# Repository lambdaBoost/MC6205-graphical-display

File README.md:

# MC6205-graphical-display
graphical display on old neon plasma screen. 

<p align="center">
  
  <figcaption><i>I'm showing this because it's funny - tracking wrecked Soviet era vehicles on a Soviet era device. Also, note the dead display line on the 'abandoned' section. We'll fix that later.</i></figcaption>
</p>

This is a two part project using the Soviet Ukrainian MC6205 plasma display.
Part 1 uses the unaltered device with an ESP32 in order to display text info from any suitable webpage or API.
Part 2 will convert the device into a full graphical display (ie not just text).

## MC6205 Intro
The device itself is a monochrome neon plasma display, produced throughout the 1980s and early 1990s in Soviet Ukraine. It is capable of displaying text on a 100x100px screen. This is achieved by supplying appropriate serial inputs to the 64 pin connector on the base of the display.
Included in the package is an EEPROM which converts the serial inputs into text characters. This unfortunately mean the MC6205 is only capable of displaying text, but part 2 will see me re-wiring and adding a custom PCB to allow for full graphical display.

## Vehicle Loss Tracker
To demo part 1, I'm using the device to provide live updates on Russian vehicle losses. Data is from the excellent [Oryx loss tracker](https://www.oryxspioenkop.com/2022/02/attack-on-europe-documenting-equipment.html)

Fortunately someone else did the hard work and wrote an arduino library [arduino library](https://github.com/holzachr/MS6205-arduino-library) to display text to the display, so all I needed to do was hook it up to the ESP32 (following the instructions from the linked repo).

Data is provided by a custom API which runs on a seperate machine. In my case, the API runs from a raspberry pi and is queried by the ESP32. This avoided having to attempt to parse the webpage in Arduino...which would be a nightmare. The code for part 2 will be in Micropython which I find much easier to work with.

For now, the setup is wired up via a breadboard. When part 2 is complete it will be entirely contained in the original enclosure.

<p align="center">
  
  <figcaption><i>It's a clock too, because why not.</i></figcaption>
</p>

## Prerequisites
To build the vehicle tracker display in the exact format shown here you will need:

* MC6205 display. Available on ebay...but they are gradually getting more and more expensive!
* Raspberry pi with docker installed
* SN74HC595 shift register
* ESP32 WROOM development board
* A lot of hookup wire
* [MS6205-arduino-library](https://github.com/holzachr/MS6205-arduino-library) installed in your Arduino libraries folder
* 12v power supply (mine is 1A)

## Instructions
To build the vehicle loss tracker do the following:

* Hook up the MC6205 to the ESP32 and 12v power supply as detailed in [holzachr's repo](https://github.com/holzachr/MS6205-arduino-library)
* clone this repo to the raspberry pi
* on the pi, cd into the web-scraper directory
* then build and run the docker container with: `docker-compose up -d`
* the API should now be active - note the pi's IP address (`ifconfig`)
* open the file at /mc6205/vehicle_loss_tracker.ino
* edit the first 3 lines (after the library imports) to include the correct IP address for the pi, your wifi network SSID and your wifi password (this is a lazy way of getting credentials - I'll add a proper wifi manager later).
* upload the edited .ino file to the esp32. I had to disconnect GPIO12 during the upload for it to work.
* Enjoy!

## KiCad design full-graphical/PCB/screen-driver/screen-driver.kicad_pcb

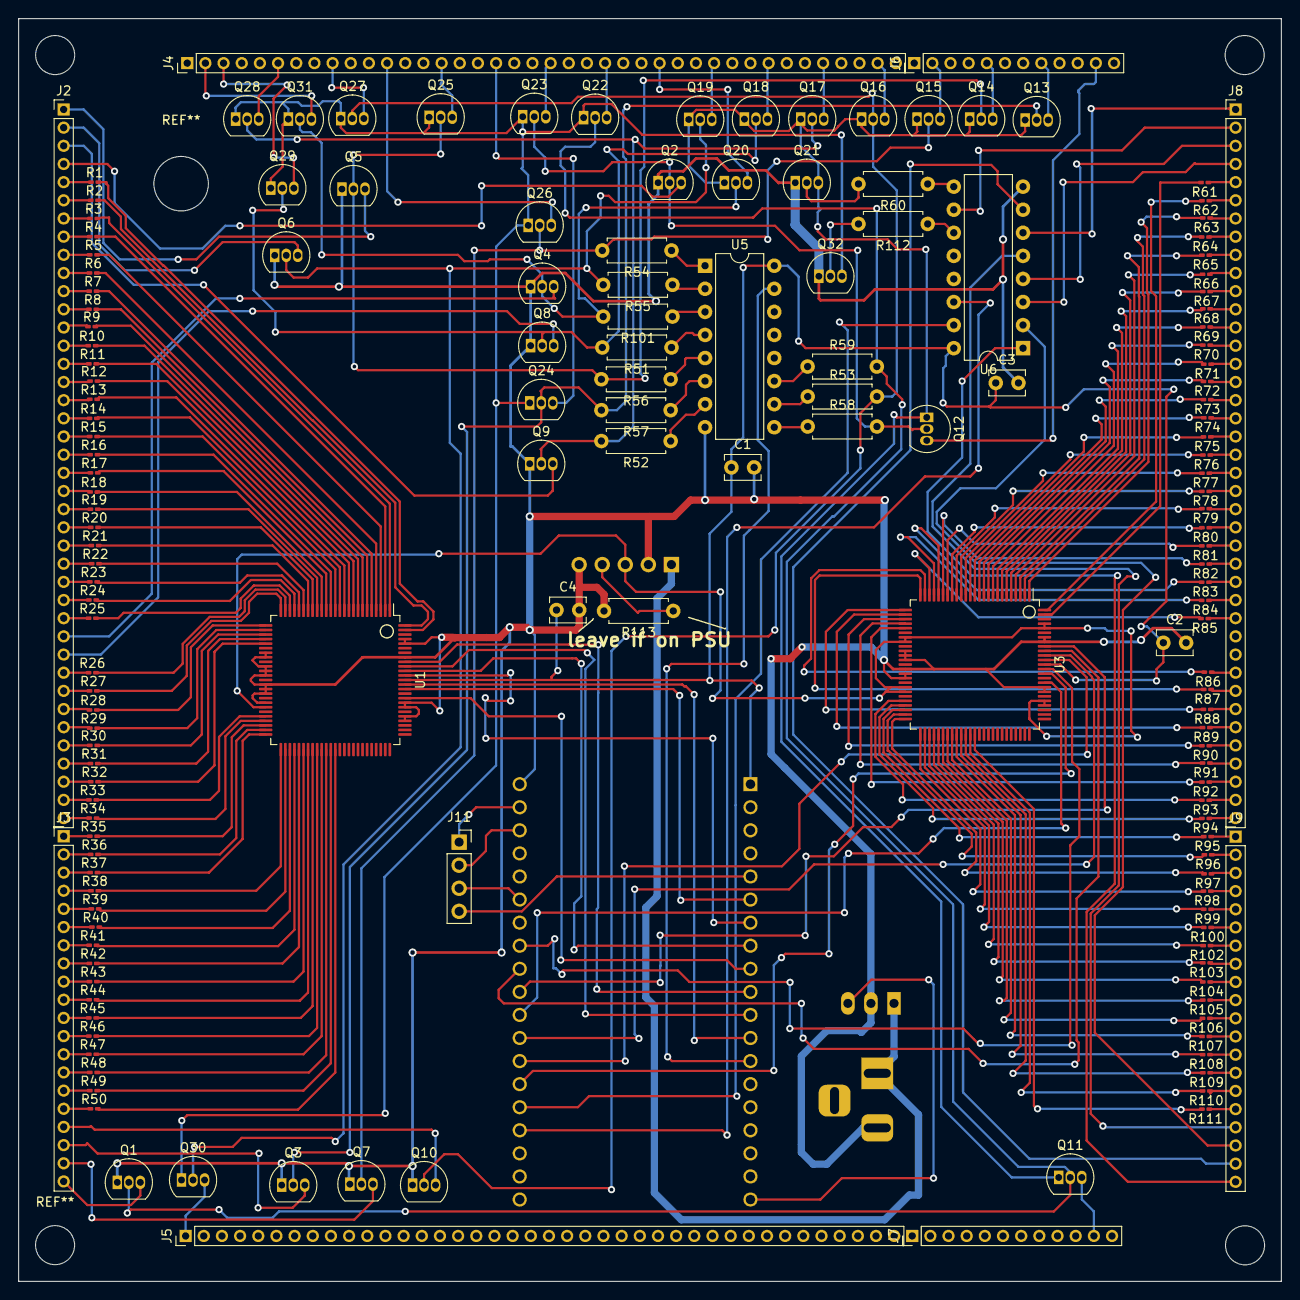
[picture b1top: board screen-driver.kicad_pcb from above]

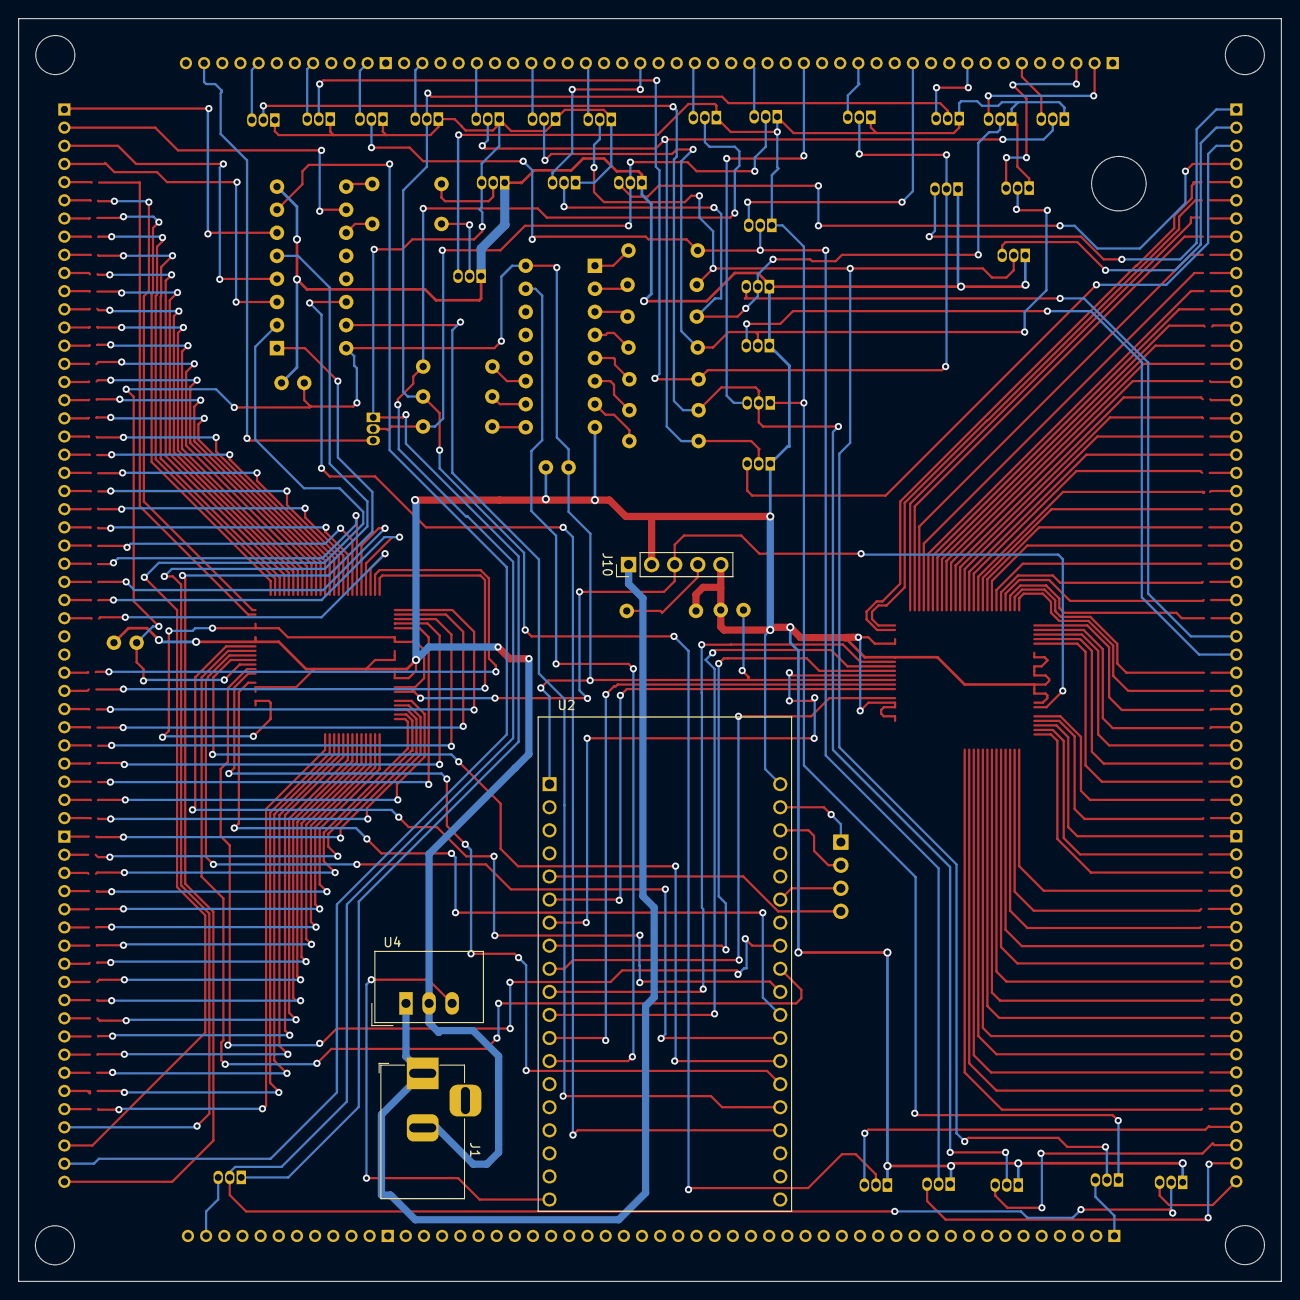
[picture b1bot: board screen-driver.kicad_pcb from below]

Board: 2 copper layers, 139.0 x 139.0 mm, 166 parts (4 on the bottom side), 291 nets.

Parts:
C1, C2, C3, C4: C_Small; C_Disc_D3.8mm_W2.6mm_P2.50mm
J1: Barrel_Jack_Switch; BarrelJack_Horizontal
J2: ANODE - EVEN 2-60; PinHeader_1x40_P2.00mm_Vertical
J3: ANODE - EVEN-62-100; PinHeader_1x20_P2.00mm_Vertical
J4: CATHODE - EVEN - 42-100; PinHeader_1x40_P2.00mm_Vertical
J5: CATHODE ODD 41-99; PinHeader_1x40_P2.00mm_Vertical
J6: CATHODE EVEN 2-40; PinHeader_1x12_P2.00mm_Vertical
J7: CATHODE ODD 1-39; PinHeader_1x12_P2.00mm_Vertical
J8: ANODE - ODD 1-59; PinHeader_1x40_P2.00mm_Vertical
J9: ANODE - ODD 61-99; PinHeader_1x20_P2.00mm_Vertical
J10: Conn_01x05_Male; PinHeader_1x05_P2.54mm_Vertical
J11: Conn_01x04; PinSocket_1x04_P2.54mm_Vertical
Q1, Q2, Q3, Q4, Q5, Q6, Q7, Q8, Q9, Q10, Q11, Q12, Q13, Q14, Q15, Q16, Q17, Q18, Q19, Q20, Q21, Q22, Q23, Q24, Q25, Q26, Q27, Q28, Q29, Q30, Q31, Q32: MPSA42; TO-92_Inline
R1, R2, R3, R4, R5, R6, R7, R8, R9, R10, R11, R12, R13, R14, R15, R16, R17, R18, R19, R20, R21, R22, R23, R24, R25, R26, R27, R28, R29, R30, R31, R32, R33, R34, R35, R36, R37, R38, R39, R40, R41, R42, R43, R44, R45, R46, R47, R48, R49, R50, R61, R62, R63, R64, R65, R66, R67, R68, R69, R70, R71, R72, R73, R74, R75, R76, R77, R78, R79, R80, R81, R82, R83, R84, R85, R86, R87, R88, R89, R90, R91, R92, R93, R94, R95, R96, R97, R98, R99, R100, R102, R103, R104, R105, R106, R107, R108, R109, R110, R111: R; R_0201_0603Metric_Pad0.64x0.40mm_HandSolder
R51, R52, R53, R54, R55, R56, R57, R58, R59, R60, R101, R112, R113: R; R_Axial_DIN0207_L6.3mm_D2.5mm_P7.62mm_Horizontal
U1, U3: SN755870; TQFP-100_14x14mm_P0.5mm
U2: ESP32-DEVKITC-32D; MODULE_ESP32-DEVKITC-32D
U4: TSR_1-2450; Converter_DCDC_TRACO_TSR-1_THT
U5, U6: CD4017BE; DIP-16_W7.62mm

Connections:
+3V3: C1.1, C2.1, C3.1, C4.1, U1.88 (VDD), U2.1 (3V3), U3.88 (VDD), U5.16 (VDD), U6.16 (VDD)
+5V: U2.19 (EXT_5V), U4.3 (Vout)
GND: C1.2, C2.2, C3.2, C4.2, J1.2, J10.2, J10.5, Q1.1 (E), Q2.1 (E), Q3.1 (E), Q4.1 (E), Q5.1 (E), Q6.1 (E), Q7.1 (E), Q8.1 (E), Q9.1 (E), Q10.1 (E), Q21.1 (E), Q32.1 (E), R113.2, U1.32 (VDDH), U1.33 (VDDH), U1.35 (GND1), U1.36 (GND1), U1.37 (GND1), U1.39 (GND2), U1.40 (GND1), U1.41 (GND1), U1.43 (VDDH), U1.79 (VDDH), U1.80 (VDDH), U1.82 (GND1), U1.83 (GND1), U1.93 (GND1), U1.96 (VDDH), U1.97 (VDDH), U2.20 (GND3), U3.35 (GND1), U3.36 (GND1), U3.37 (GND1), U3.39 (GND2), U3.40 (GND1), U3.41 (GND1), U3.82 (GND1), U3.83 (GND1), U3.93 (GND1), U3.94 (GND1), U4.2 (GND), U5.8 (VSS), U6.8 (VSS)
unnamed: J1.1, J10.1, U4.1 (Vin)
unnamed: J2.1, Q5.3 (C)
unnamed: J2.2, Q6.3 (C)
unnamed: J2.3, Q9.3 (C)
unnamed: J2.4, Q2.3 (C)
unnamed: J2.5, R1.1
unnamed: J2.6, R2.1
unnamed: J2.7, R3.1
unnamed: J2.8, R4.1
unnamed: J2.9, R5.1
unnamed: J2.10, R6.1
unnamed: J2.11, R7.1
unnamed: J2.12, R8.1
unnamed: J2.13, R9.1
unnamed: J2.14, R10.1
unnamed: J2.15, R11.1
unnamed: J2.16, R12.1
unnamed: J2.17, R13.1
unnamed: J2.18, R14.1
unnamed: J2.19, R15.1
unnamed: J2.20, R16.1
unnamed: J2.21, R17.1
unnamed: J2.22, R18.1
unnamed: J2.23, R19.1
unnamed: J2.24, R20.1
unnamed: J2.25, R21.1
unnamed: J2.26, R22.1
unnamed: J2.27, R23.1
unnamed: J2.28, R24.1
unnamed: J2.29, R25.1
unnamed: J2.30, Q4.3 (C)
unnamed: J2.31, Q8.3 (C)
unnamed: J2.32, R26.1
unnamed: J2.33, R27.1
unnamed: J2.34, R28.1
unnamed: J2.35, R29.1
unnamed: J2.36, R30.1
unnamed: J2.37, R31.1
unnamed: J2.38, R32.1
unnamed: J2.39, R33.1
unnamed: J2.40, R34.1
unnamed: J3.1, R35.1
unnamed: J3.2, R36.1
unnamed: J3.3, R37.1
unnamed: J3.4, R38.1
unnamed: J3.5, R39.1
unnamed: J3.6, R40.1
unnamed: J3.7, R41.1
unnamed: J3.8, R42.1
unnamed: J3.9, R43.1
unnamed: J3.10, R44.1
unnamed: J3.11, R45.1
unnamed: J3.12, R46.1
unnamed: J3.13, R47.1
unnamed: J3.14, R48.1
unnamed: J3.15, R49.1
unnamed: J3.16, R50.1
unnamed: J3.17, Q10.3 (C)
unnamed: J3.18, Q3.3 (C)
unnamed: J3.19, Q7.3 (C)
unnamed: J3.20, Q1.3 (C)
unnamed: J4.2, Q31.3 (C)
unnamed: J4.3, Q29.3 (C)
unnamed: J4.6, Q28.3 (C)
unnamed: J4.9, Q27.3 (C)
unnamed: J4.12, Q26.3 (C)
unnamed: J4.15, Q25.3 (C)
unnamed: J4.18, Q24.3 (C)
unnamed: J4.21, Q23.3 (C)
unnamed: J4.24, Q22.3 (C)
unnamed: J4.27, Q20.3 (C)
unnamed: J4.30, Q19.3 (C)
unnamed: J4.33, Q18.3 (C)
unnamed: J4.36, Q17.3 (C)
unnamed: J4.39, Q16.3 (C)
unnamed: J5.1, Q30.3 (C)
unnamed: J6.2, Q15.3 (C)
unnamed: J6.5, Q14.3 (C)
unnamed: J6.8, Q13.3 (C)
unnamed: J6.11, Q12.3 (C)
unnamed: J7.11, Q11.3 (C)
unnamed: J8.1, U6.6 (7)
unnamed: J8.2, U6.10 (4)
unnamed: J8.3, U6.4 (2)
unnamed: J8.4, U6.3 (O)
unnamed: J8.5, R61.1
unnamed: J8.6, R62.1
unnamed: J8.7, R63.1
unnamed: J8.8, R64.1
unnamed: J8.9, R65.1
unnamed: J8.10, R66.1
unnamed: J8.11, R67.1
unnamed: J8.12, R68.1
unnamed: J8.13, R69.1
unnamed: J8.14, R70.1
unnamed: J8.15, R71.1
unnamed: J8.16, R72.1
unnamed: J8.17, R73.1
unnamed: J8.18, R74.1
unnamed: J8.19, R75.1
unnamed: J8.20, R76.1
unnamed: J8.21, R77.1
unnamed: J8.22, R78.1
unnamed: J8.23, R79.1
unnamed: J8.24, R80.1
unnamed: J8.25, R81.1
unnamed: J8.26, R82.1
unnamed: J8.27, R83.1
unnamed: J8.28, R84.1
unnamed: J8.29, R85.1
unnamed: J8.32, R86.1
unnamed: J8.33, R87.1
unnamed: J8.34, R88.1
unnamed: J8.35, R89.1
unnamed: J8.36, R90.1
unnamed: J8.37, R91.1
unnamed: J8.38, R92.1
unnamed: J8.39, R93.1
unnamed: J8.40, R94.1
unnamed: J9.1, R95.1
unnamed: J9.2, R96.1
unnamed: J9.3, R97.1
unnamed: J9.4, R98.1
unnamed: J9.5, R99.1
unnamed: J9.6, R100.1
unnamed: J9.7, R102.1
unnamed: J9.8, R103.1
unnamed: J9.9, R104.1
unnamed: J9.10, R105.1
unnamed: J9.11, R106.1
unnamed: J9.12, R107.1
unnamed: J9.13, R108.1
unnamed: J9.14, R109.1
unnamed: J9.15, R110.1
unnamed: J9.16, R111.1
unnamed: J9.17, U6.5 (6)
unnamed: J9.18, U6.2 (1)
unnamed: J9.19, U6.7 (3)
unnamed: J9.20, U6.1 (5)
unnamed: J10.3, U1.44 (VDDH), U3.32 (VDDH), U3.33 (VDDH), U3.43 (VDDH), U3.44 (VDDH), U3.79 (VDDH), U3.80 (VDDH), U3.96 (VDDH), U3.97 (VDDH)
unnamed: J10.4, R113.1
unnamed: Q1.2 (B), Q11.2 (B), Q22.2 (B), R59.2
unnamed: Q10.2 (B), Q16.2 (B), Q27.2 (B), R53.2
unnamed: Q11.1 (E), Q12.1 (E), Q13.1 (E), Q14.1 (E), Q15.1 (E), Q16.1 (E), Q17.1 (E), Q18.1 (E), Q19.1 (E), Q20.1 (E), Q21.3 (C)
unnamed: Q2.2 (B), Q12.2 (B), Q23.2 (B), R58.2
unnamed: Q3.2 (B), Q13.2 (B), Q24.2 (B), R57.2
unnamed: Q5.2 (B), Q14.2 (B), Q25.2 (B), R56.2
unnamed: Q7.2 (B), Q15.2 (B), Q26.2 (B), R54.2
unnamed: Q9.2 (B), Q17.2 (B), Q28.2 (B), R52.2
unnamed: Q8.2 (B), Q18.2 (B), Q29.2 (B), R51.2
unnamed: Q6.2 (B), Q19.2 (B), Q30.2 (B), R55.2
unnamed: Q4.2 (B), Q20.2 (B), Q31.2 (B), R101.2
unnamed: Q21.2 (B), R60.2
unnamed: Q22.1 (E), Q23.1 (E), Q24.1 (E), Q25.1 (E), Q26.1 (E), Q27.1 (E), Q28.1 (E), Q29.1 (E), Q30.1 (E), Q31.1 (E), Q32.3 (C)
unnamed: Q32.2 (B), R112.2
unnamed: R1.2, U1.99 (OUT1)
unnamed: R2.2, U1.100 (OUT2)
unnamed: R3.2, U1.1 (OUT3)
unnamed: R4.2, U1.2 (OUT4)
unnamed: R5.2, U1.3 (OUT5)
unnamed: R6.2, U1.4 (OUT6)
unnamed: R7.2, U1.5 (OUT7)
unnamed: R8.2, U1.6 (OUT8)
unnamed: R9.2, U1.7 (OUT9)
unnamed: R10.2, U1.8 (OUT10)
unnamed: R11.2, U1.9 (OUT11)
unnamed: R12.2, U1.10 (OUT12)
unnamed: R13.2, U1.11 (OUT13)
unnamed: R14.2, U1.12 (OUT14)
unnamed: R15.2, U1.13 (OUT15)
unnamed: R16.2, U1.14 (OUT16)
unnamed: R17.2, U1.15 (OUT17)
unnamed: R18.2, U1.16 (OUT18)
unnamed: R19.2, U1.17 (OUT19)
unnamed: R20.2, U1.18 (OUT20)
unnamed: R21.2, U1.19 (OUT21)
unnamed: R22.2, U1.20 (OUT22)
unnamed: R23.2, U1.21 (OUT23)
unnamed: R24.2, U1.22 (OUT24)
unnamed: R25.2, U1.23 (OUT25)
unnamed: R26.2, U1.24 (OUT26)
unnamed: R27.2, U1.25 (OUT27)
unnamed: R28.2, U1.26 (OUT28)
unnamed: R29.2, U1.27 (OUT29)
unnamed: R30.2, U1.28 (OUT30)
unnamed: R31.2, U1.29 (OUT31)
unnamed: R32.2, U1.30 (OUT32)
unnamed: R33.2, U1.46 (OUT33)
unnamed: R34.2, U1.47 (OUT34)
unnamed: R35.2, U1.48 (OUT35)
unnamed: R36.2, U1.49 (OUT36)
unnamed: R37.2, U1.50 (OUT37)
unnamed: R38.2, U1.51 (OUT38)
unnamed: R39.2, U1.52 (OUT39)
unnamed: R40.2, U1.53 (OUT40)
unnamed: R41.2, U1.54 (OUT41)
unnamed: R42.2, U1.55 (OUT42)
unnamed: R43.2, U1.56 (OUT43)
unnamed: R44.2, U1.57 (OUT44)
unnamed: R45.2, U1.58 (OUT45)
unnamed: R46.2, U1.59 (OUT46)
unnamed: R47.2, U1.60 (OUT47)
unnamed: R48.2, U1.61 (OUT48)
unnamed: R49.2, U1.62 (OUT49)
unnamed: R50.2, U1.63 (OUT50)
unnamed: R51.1, U5.4 (2)
unnamed: R52.1, U5.7 (3)
unnamed: R53.1, U5.10 (4)
unnamed: R54.1, U5.1 (5)
unnamed: R55.1, U5.2 (1)
unnamed: R56.1, U5.5 (6)
unnamed: R57.1, U5.6 (7)
unnamed: R58.1, U5.9 (8)
unnamed: R59.1, U5.11 (9)
unnamed: R60.1, U6.9 (8)
unnamed: R61.2, U3.99 (OUT1)
unnamed: R62.2, U3.100 (OUT2)
unnamed: R63.2, U3.1 (OUT3)
unnamed: R64.2, U3.2 (OUT4)
unnamed: R65.2, U3.3 (OUT5)
unnamed: R66.2, U3.4 (OUT6)
unnamed: R67.2, U3.5 (OUT7)
unnamed: R68.2, U3.6 (OUT8)
unnamed: R69.2, U3.7 (OUT9)
unnamed: R70.2, U3.8 (OUT10)
unnamed: R71.2, U3.9 (OUT11)
unnamed: R72.2, U3.10 (OUT12)
unnamed: R73.2, U3.11 (OUT13)
unnamed: R74.2, U3.12 (OUT14)
unnamed: R75.2, U3.13 (OUT15)
unnamed: R76.2, U3.14 (OUT16)
unnamed: R77.2, U3.15 (OUT17)
unnamed: R78.2, U3.16 (OUT18)
unnamed: R79.2, U3.17 (OUT19)
unnamed: R80.2, U3.18 (OUT20)
unnamed: R81.2, U3.19 (OUT21)
unnamed: R82.2, U3.20 (OUT22)
unnamed: R83.2, U3.21 (OUT23)
unnamed: R84.2, U3.22 (OUT24)
unnamed: R85.2, U3.23 (OUT25)
unnamed: R86.2, U3.24 (OUT26)
unnamed: R87.2, U3.25 (OUT27)
unnamed: R88.2, U3.26 (OUT28)
unnamed: R89.2, U3.27 (OUT29)
unnamed: R90.2, U3.28 (OUT30)
unnamed: R91.2, U3.29 (OUT31)
unnamed: R92.2, U3.30 (OUT32)
unnamed: R93.2, U3.46 (OUT33)
unnamed: R94.2, U3.47 (OUT34)
unnamed: R95.2, U3.48 (OUT35)
unnamed: R96.2, U3.49 (OUT36)
unnamed: R97.2, U3.50 (OUT37)
unnamed: R98.2, U3.51 (OUT38)
unnamed: R99.2, U3.52 (OUT39)
unnamed: R100.2, U3.53 (OUT40)
unnamed: R101.1, U5.3 (O)
unnamed: R102.2, U3.54 (OUT41)
unnamed: R103.2, U3.55 (OUT42)
unnamed: R104.2, U3.56 (OUT43)
unnamed: R105.2, U3.57 (OUT44)
unnamed: R106.2, U3.58 (OUT45)
unnamed: R107.2, U3.59 (OUT46)
unnamed: R108.2, U3.60 (OUT47)
unnamed: R109.2, U3.61 (OUT48)
unnamed: R110.2, U3.62 (OUT49)
unnamed: R111.2, U3.63 (OUT50)
unnamed: R112.1, U6.11 (9)
unnamed: U1.84 (DIR), U2.9 (IO25)
unnamed: U1.86 (CLK), U2.6 (IO35)
unnamed: U1.87 (LAT), U2.12 (IO14)
unnamed: U1.89 (OC1), U2.7 (IO32)
unnamed: U1.90 (OC2), U2.8 (IO33)
unnamed: U1.91 (SI), U2.11 (IO27)
unnamed: U1.92 (CLR), U2.10 (IO26)
unnamed: J11.4, U2.5 (IO34)
unnamed: J11.1, U2.21 (IO23)
unnamed: J11.2, U2.22 (IO22)
unnamed: J11.3, U2.25 (IO21)
unnamed: U2.27 (IO19), U3.87 (LAT)
unnamed: U2.28 (IO18), U3.91 (SI)
unnamed: U2.29 (IO5), U3.92 (CLR)
unnamed: U2.30 (IO17), U3.84 (DIR)
unnamed: U2.31 (IO16), U3.90 (OC2)
unnamed: U2.32 (IO4), U3.89 (OC1)
unnamed: U2.33 (IO0), U3.86 (CLK)
unnamed: U2.34 (IO2), U6.15 (RESET)
unnamed: U2.35 (IO15), U6.14 (CLOCK)
unnamed: U2.13 (IO12), U5.15 (RESET)

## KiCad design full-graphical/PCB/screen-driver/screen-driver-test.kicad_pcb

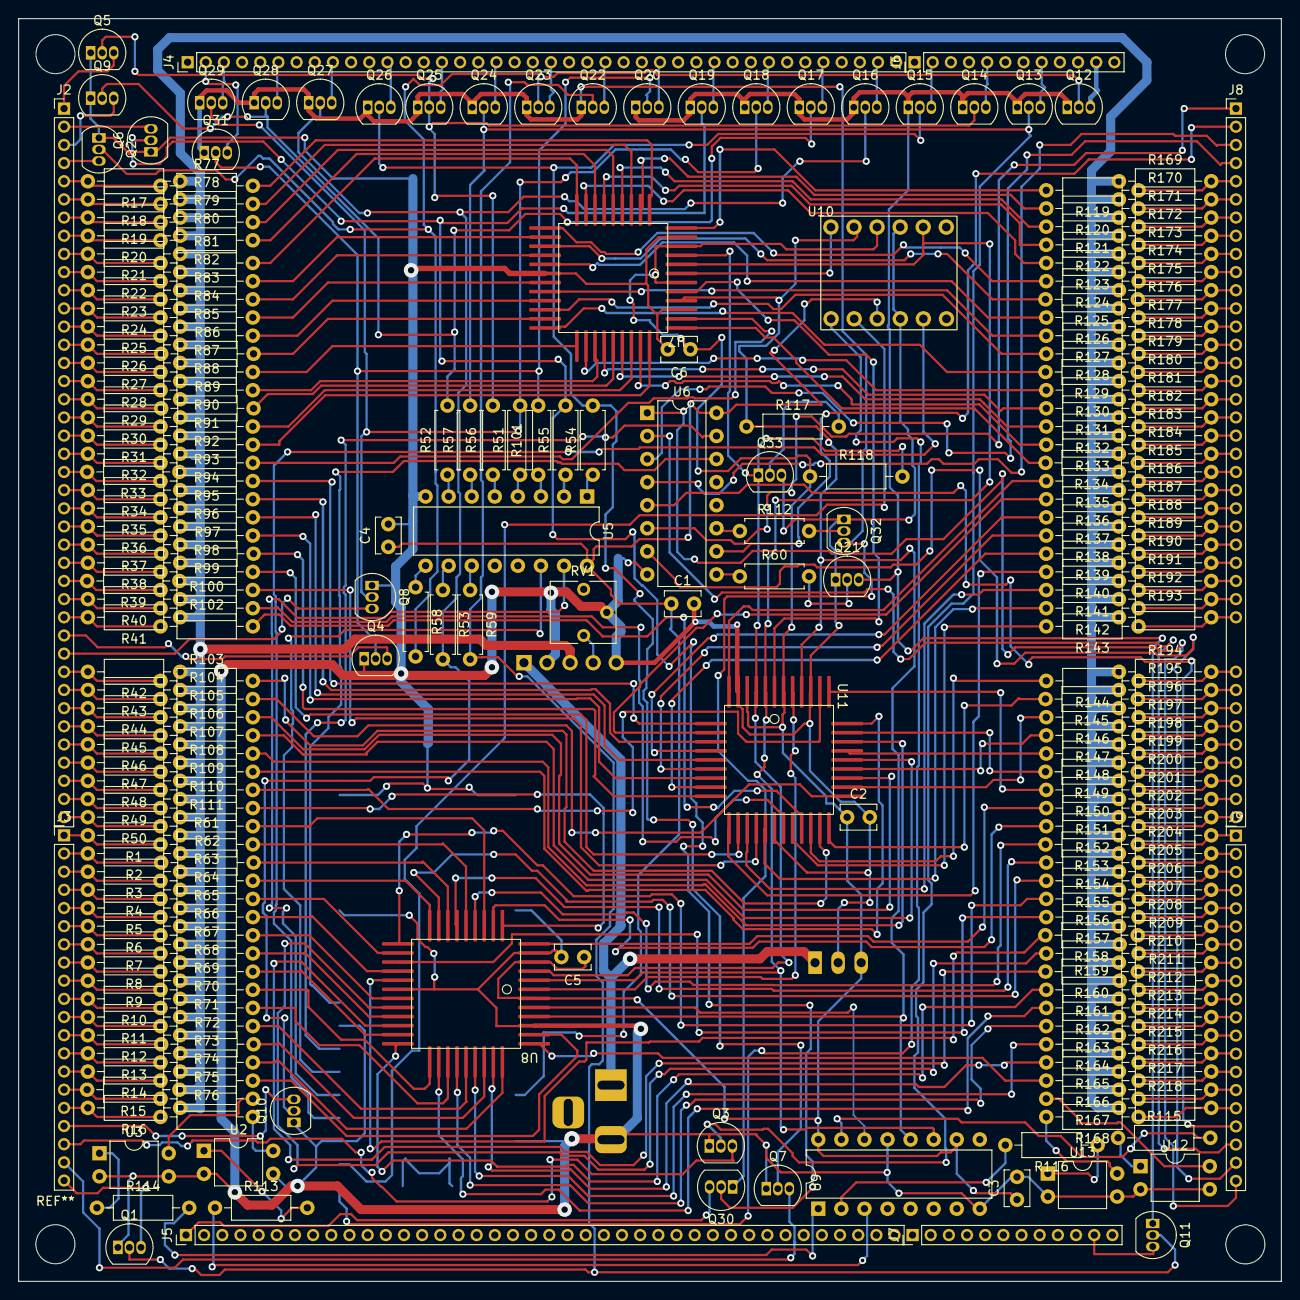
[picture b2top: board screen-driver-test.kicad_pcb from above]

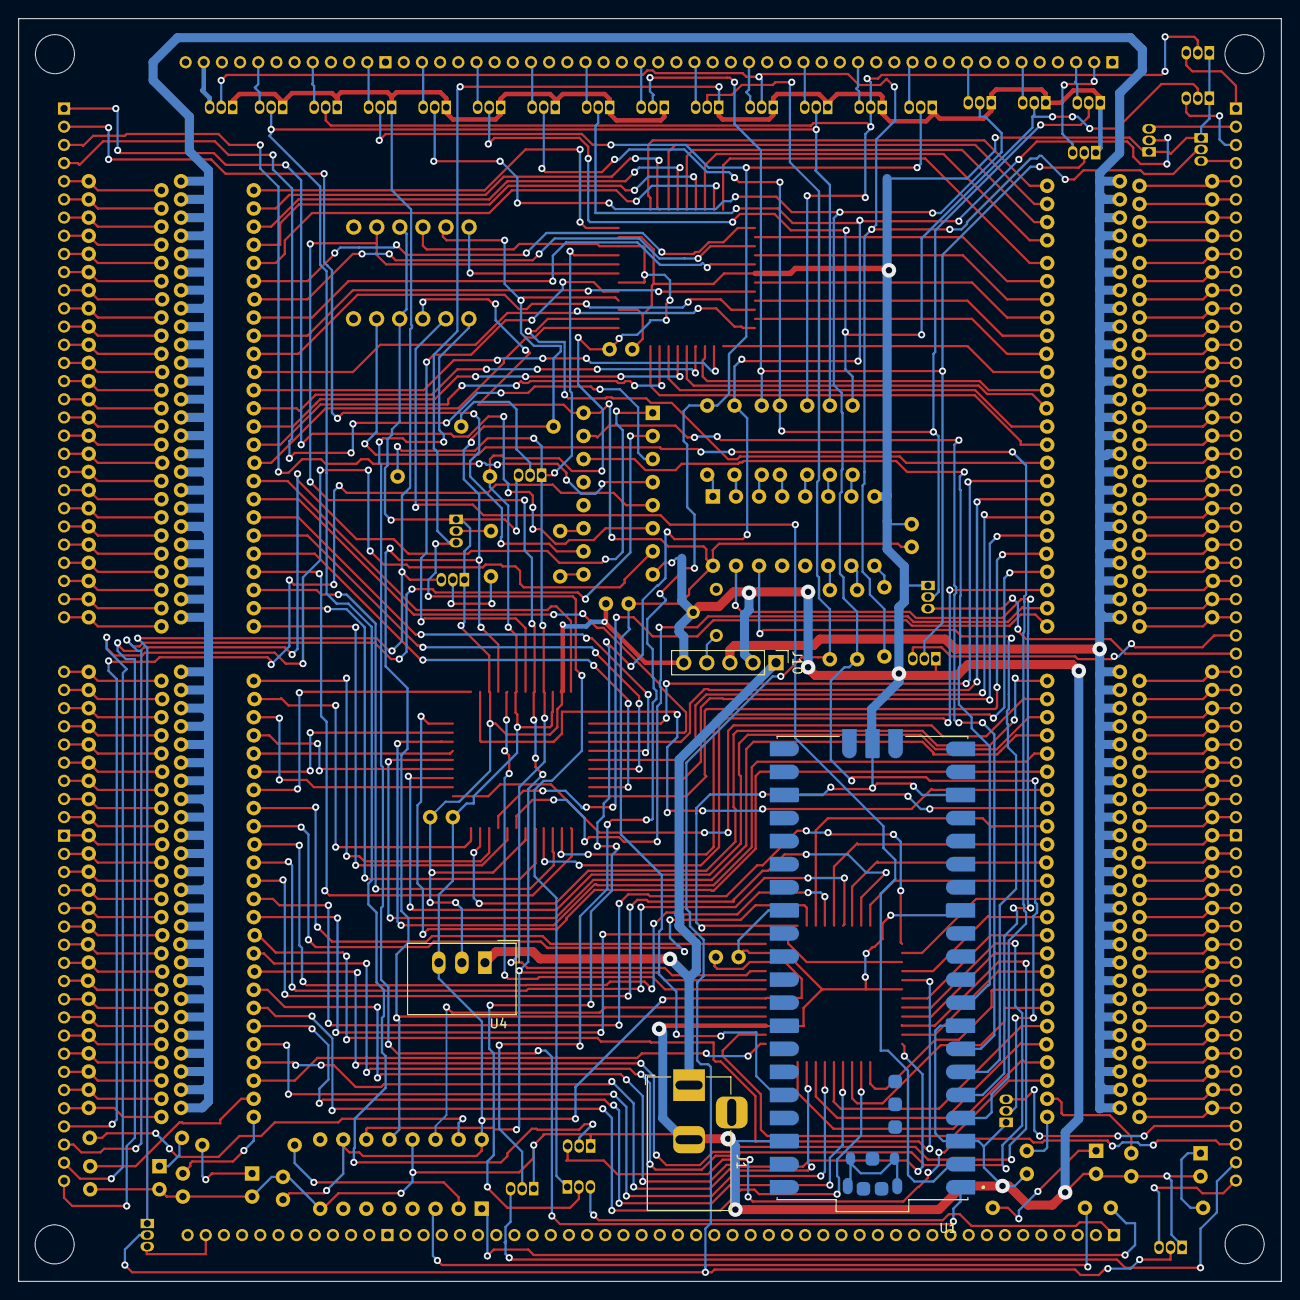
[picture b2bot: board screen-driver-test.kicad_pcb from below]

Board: 2 copper layers, 139.0 x 139.0 mm, 281 parts (4 on the bottom side), 294 nets.

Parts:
C1, C2, C3, C4, C5, C6: C_Small; C_Disc_D3.8mm_W2.6mm_P2.50mm
J1: Barrel_Jack_Switch; BarrelJack_Horizontal
J2: ANODE - EVEN 2-60; PinHeader_1x40_P2.00mm_Vertical
J3: ANODE - EVEN-62-100; PinHeader_1x20_P2.00mm_Vertical
J4: CATHODE - EVEN - 42-100; PinHeader_1x40_P2.00mm_Vertical
J5: CATHODE ODD 41-99; PinHeader_1x40_P2.00mm_Vertical
J6: CATHODE EVEN 2-40; PinHeader_1x12_P2.00mm_Vertical
J7: CATHODE ODD 1-39; PinHeader_1x12_P2.00mm_Vertical
J8: ANODE - ODD 1-59; PinHeader_1x40_P2.00mm_Vertical
J9: ANODE - ODD 61-99; PinHeader_1x20_P2.00mm_Vertical
J10: Conn_01x05_Male; PinHeader_1x05_P2.54mm_Vertical
Q1, Q2, Q3, Q4, Q5, Q6, Q7, Q8, Q9, Q10, Q11, Q12, Q13, Q14, Q15, Q16, Q17, Q18, Q19, Q20, Q21, Q22, Q23, Q24, Q25, Q26, Q27, Q28, Q29, Q30, Q31, Q32: MPSA42; TO-92_Inline
Q33: BC547; TO-92_Inline
R1, R2, R3, R4, R5, R6, R7, R8, R9, R10, R11, R12, R13, R14, R15, R16, R17, R18, R19, R20, R21, R22, R23, R24, R25, R26, R27, R28, R29, R30, R31, R32, R33, R34, R35, R36, R37, R38, R39, R40, R41, R42, R43, R44, R45, R46, R47, R48, R49, R50, R169, R170, R171, R172, R173, R174, R175, R176, R177, R178, R179, R180, R181, R182, R183, R184, R185, R186, R187, R188, R189, R190, R191, R192, R193, R194, R195, R196, R197, R198, R199, R200, R201, R202, R203, R204, R205, R206, R207, R208, R209, R210, R211, R212, R213, R214, R215, R216, R217, R218: 390k; R_Axial_DIN0207_L6.3mm_D2.5mm_P10.16mm_Horizontal
R51, R52, R53, R54, R55, R56, R57, R58, R59, R60, R101, R112: R; R_Axial_DIN0207_L6.3mm_D2.5mm_P7.62mm_Horizontal
R61, R62, R63, R64, R65, R66, R67, R68, R69, R70, R71, R72, R73, R74, R75, R76, R77, R78, R79, R80, R81, R82, R83, R84, R85, R86, R87, R88, R89, R90, R91, R92, R93, R94, R95, R96, R97, R98, R99, R100, R102, R103, R104, R105, R106, R107, R108, R109, R110, R111, R119, R120, R121, R122, R123, R124, R125, R126, R127, R128, R129, R130, R131, R132, R133, R134, R135, R136, R137, R138, R139, R140, R141, R142, R143, R144, R145, R146, R147, R148, R149, R150, R151, R152, R153, R154, R155, R156, R157, R158, R159, R160, R161, R162, R163, R164, R165, R166, R167, R168: 330k; R_Axial_DIN0207_L6.3mm_D2.5mm_P10.16mm_Horizontal
R113, R114, R115, R116: 330; R_Axial_DIN0207_L6.3mm_D2.5mm_P10.16mm_Horizontal
R117: 10k; R_Axial_DIN0207_L6.3mm_D2.5mm_P10.16mm_Horizontal
R118: 100; R_Axial_DIN0207_L6.3mm_D2.5mm_P10.16mm_Horizontal
RV1: R_Potentiometer; Potentiometer_Vishay_T73YP_Vertical
U1: SC0915; MODULE_SC0915
U2, U3, U12, U13: TLP627; DIP-4_W7.62mm
U4: TSR_1-2450; Converter_DCDC_TRACO_TSR-1_THT
U5, U6: CD4017BE; DIP-16_W7.62mm
U7, U8, U11: YH5504KH01
U9: 74HC595; DIP-16_W7.62mm
U10: level_converter; level_shifter

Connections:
+3V3: C1.1, C4.1, U1.36 (3V3_OUT), U5.16 (VDD), U6.16 (VDD), U10.3 (LV_in)
+5V: C2.1, C3.1, C5.1, C6.1, R118.1, U4.3 (Vout), U7.4 (VCC), U7.42 (VCC), U8.4 (VCC), U8.42 (VCC), U9.10 (~SRCLR), U9.16 (VCC), U10.10 (HV_in), U11.4 (VCC), U11.42 (VCC)
/clk: U7.2 (clk), U8.2 (clk), U9.11 (SRCLK), U10.8 (HV3), U11.2 (clk)
GND: C1.2, C2.2, C3.2, C4.2, C5.2, C6.2, J1.2, J10.2, J10.5, Q1.1 (E), Q2.1 (E), Q3.1 (E), Q4.1 (E), Q5.1 (E), Q6.1 (E), Q7.1 (E), Q8.1 (E), Q9.1 (E), Q10.1 (E), Q21.1 (E), Q32.1 (E), Q33.3 (E), RV1.2, U1.3 (GND), U1.8 (GND), U1.13 (GND), U1.18 (GND), U1.23 (GND), U1.28 (GND), U1.38 (GND), U1.D2 (GND), U2.2, U2.3, U3.2, U3.3, U4.2 (GND), U5.8 (VSS), U6.8 (VSS), U7.5 (gnd), U7.21 (gnd), U7.39 (gnd), U8.5 (gnd), U8.21 (gnd), U8.39 (gnd), U9.8 (GND), U9.13 (~OE), U10.4 (GND), U10.9 (GND), U11.5 (gnd), U11.21 (gnd), U11.39 (gnd), U12.2, U12.3, U13.2, U13.3
unnamed: J1.1, J10.1, U4.1 (Vin)
unnamed: J2.1, Q5.3 (C)
unnamed: J2.2, Q6.3 (C)
unnamed: J2.3, Q9.3 (C)
unnamed: J2.4, Q2.3 (C)
unnamed: J2.5, R17.2, R77.1
unnamed: J2.6, R18.2, R78.1
unnamed: J2.7, R19.2, R79.1
unnamed: J2.8, R20.2, R80.1
unnamed: J2.9, R21.2, R81.1
unnamed: J2.10, R22.2, R82.1
unnamed: J2.11, R23.2, R83.1
unnamed: J2.12, R24.2, R84.1
unnamed: J2.13, R25.2, R85.1
unnamed: J2.14, R26.2, R86.1
unnamed: J2.15, R27.2, R87.1
unnamed: J2.16, R28.2, R88.1
unnamed: J2.17, R29.2, R89.1
unnamed: J2.18, R30.2, R90.1
unnamed: J2.19, R31.2, R91.1
unnamed: J2.20, R32.2, R92.1
unnamed: J2.21, R33.2, R93.1
unnamed: J2.22, R34.2, R94.1
unnamed: J2.23, R35.2, R95.1
unnamed: J2.24, R36.2, R96.1
unnamed: J2.25, R37.2, R97.1
unnamed: J2.26, R38.2, R98.1
unnamed: J2.27, R39.2, R99.1
unnamed: J2.28, R40.2, R100.1
unnamed: J2.29, R41.2, R102.1
unnamed: J2.32, R42.2, R103.1
unnamed: J2.33, R43.2, R104.1
unnamed: J2.34, R44.2, R105.1
unnamed: J2.35, R45.2, R106.1
unnamed: J2.36, R46.2, R107.1
unnamed: J2.37, R47.2, R108.1
unnamed: J2.38, R48.2, R109.1
unnamed: J2.39, R49.2, R110.1
unnamed: J2.40, R50.2, R111.1
unnamed: J3.1, R1.2, R61.1
unnamed: J3.2, R2.2, R62.1
unnamed: J3.3, R3.2, R63.1
unnamed: J3.4, R4.2, R64.1
unnamed: J3.5, R5.2, R65.1
unnamed: J3.6, R6.2, R66.1
unnamed: J3.7, R7.2, R67.1
unnamed: J3.8, R8.2, R68.1
unnamed: J3.9, R9.2, R69.1
unnamed: J3.10, R10.2, R70.1
unnamed: J3.11, R11.2, R71.1
unnamed: J3.12, R12.2, R72.1
unnamed: J3.13, R13.2, R73.1
unnamed: J3.14, R14.2, R74.1
unnamed: J3.15, R15.2, R75.1
unnamed: J3.16, R16.2, R76.1
unnamed: J3.17, Q10.3 (C)
unnamed: J3.18, Q3.3 (C)
unnamed: J3.19, Q7.3 (C)
unnamed: J3.20, Q1.3 (C)
unnamed: J5.1, Q30.3 (C)
unnamed: J7.11, Q11.3 (C)
unnamed: J8.1, U6.6 (7)
unnamed: J8.2, U6.10 (4)
unnamed: J8.3, U6.4 (2)
unnamed: J8.4, U6.3 (O)
unnamed: J8.5, R119.1, R169.2
unnamed: J8.6, R120.1, R170.2
unnamed: J8.7, R121.1, R171.2
unnamed: J8.8, R122.1, R172.2
unnamed: J8.9, R123.1, R173.2
unnamed: J8.10, R124.1, R174.2
unnamed: J8.11, R125.1, R175.2
unnamed: J8.12, R126.1, R176.2
unnamed: J8.13, R127.1, R177.2
unnamed: J8.14, R128.1, R178.2
unnamed: J8.15, R129.1, R179.2
unnamed: J8.16, R130.1, R180.2
unnamed: J8.17, R131.1, R181.2
unnamed: J8.18, R132.1, R182.2
unnamed: J8.19, R133.1, R183.2
unnamed: J8.20, R134.1, R184.2
unnamed: J8.21, R135.1, R185.2
unnamed: J8.22, R136.1, R186.2
unnamed: J8.23, R137.1, R187.2
unnamed: J8.24, R138.1, R188.2
unnamed: J8.25, R139.1, R189.2
unnamed: J8.26, R140.1, R190.2
unnamed: J8.27, R141.1, R191.2
unnamed: J8.28, R142.1, R192.2
unnamed: J8.29, R143.1, R193.2
unnamed: J8.32, R144.1, R194.2
unnamed: J8.33, R145.1, R195.2
unnamed: J8.34, R146.1, R196.2
unnamed: J8.35, R147.1, R197.2
unnamed: J8.36, R148.1, R198.2
unnamed: J8.37, R149.1, R199.2
unnamed: J8.38, R150.1, R200.2
unnamed: J8.39, R151.1, R201.2
unnamed: J8.40, R152.1, R202.2
unnamed: J9.1, R153.1, R203.2
unnamed: J9.2, R154.1, R204.2
unnamed: J9.3, R155.1, R205.2
unnamed: J9.4, R156.1, R206.2
unnamed: J9.5, R157.1, R207.2
unnamed: J9.6, R158.1, R208.2
unnamed: J9.7, R159.1, R209.2
unnamed: J9.8, R160.1, R210.2
unnamed: J9.9, R161.1, R211.2
unnamed: J9.10, R162.1, R212.2
unnamed: J9.11, R163.1, R213.2
unnamed: J9.12, R164.1, R214.2
unnamed: J9.13, R165.1, R215.2
unnamed: J9.14, R166.1, R216.2
unnamed: J9.15, R167.1, R217.2
unnamed: J9.16, R168.1, R218.2
unnamed: J9.17, U6.5 (6)
unnamed: J9.18, U6.2 (1)
unnamed: J9.19, U6.7 (3)
unnamed: J9.20, U6.1 (5)
unnamed: J10.3, R1.1, R2.1, R3.1, R4.1, R5.1, R6.1, R7.1, R8.1, R9.1, R10.1, R11.1, R12.1, R13.1, R14.1, R15.1, R16.1, R17.1, R18.1, R19.1, R20.1, R21.1, R22.1, R23.1, R24.1, R25.1, R26.1, R27.1, R28.1, R29.1, R30.1, R31.1, R32.1, R33.1, R34.1, R35.1, R36.1, R37.1, R38.1, R39.1, R40.1, R41.1, R42.1, R43.1, R44.1, R45.1, R46.1, R47.1, R48.1, R49.1, R50.1, R169.1, R170.1, R171.1, R172.1, R173.1, R174.1, R175.1, R176.1, R177.1, R178.1, R179.1, R180.1, R181.1, R182.1, R183.1, R184.1, R185.1, R186.1, R187.1, R188.1, R189.1, R190.1, R191.1, R192.1, R193.1, R194.1, R195.1, R196.1, R197.1, R198.1, R199.1, R200.1, R201.1, R202.1, R203.1, R204.1, R205.1, R206.1, R207.1, R208.1, R209.1, R210.1, R211.1, R212.1, R213.1, R214.1, R215.1, R216.1, R217.1, R218.1
unnamed: J10.4, RV1.1
unnamed: Q1.2 (B), Q11.2 (B), Q22.2 (B), R59.2
unnamed: J2.30, Q4.3 (C)
unnamed: J2.31, Q8.3 (C)
unnamed: Q10.2 (B), Q16.2 (B), Q27.2 (B), R53.2
unnamed: Q11.1 (E), Q12.1 (E), Q13.1 (E), Q14.1 (E), Q15.1 (E), Q16.1 (E), Q17.1 (E), Q18.1 (E), Q19.1 (E), Q20.1 (E), Q21.3 (C)
unnamed: Q2.2 (B), Q12.2 (B), Q23.2 (B), R58.2
unnamed: J6.11, Q12.3 (C)
unnamed: Q3.2 (B), Q13.2 (B), Q24.2 (B), R57.2
unnamed: J6.8, Q13.3 (C)
unnamed: Q5.2 (B), Q14.2 (B), Q25.2 (B), R56.2
unnamed: J6.5, Q14.3 (C)
unnamed: Q7.2 (B), Q15.2 (B), Q26.2 (B), R54.2
unnamed: J6.2, Q15.3 (C)
unnamed: J4.39, Q16.3 (C)
unnamed: Q9.2 (B), Q17.2 (B), Q28.2 (B), R52.2
unnamed: J4.36, Q17.3 (C)
unnamed: Q8.2 (B), Q18.2 (B), Q29.2 (B), R51.2
unnamed: J4.33, Q18.3 (C)
unnamed: Q6.2 (B), Q19.2 (B), Q30.2 (B), R55.2
unnamed: J4.30, Q19.3 (C)
unnamed: Q4.2 (B), Q20.2 (B), Q31.2 (B), R101.2
unnamed: J4.27, Q20.3 (C)
unnamed: Q21.2 (B), R60.2
unnamed: Q22.1 (E), Q23.1 (E), Q24.1 (E), Q25.1 (E), Q26.1 (E), Q27.1 (E), Q28.1 (E), Q29.1 (E), Q30.1 (E), Q31.1 (E), Q32.3 (C)
unnamed: J4.24, Q22.3 (C)
unnamed: J4.21, Q23.3 (C)
unnamed: J4.18, Q24.3 (C)
unnamed: J4.15, Q25.3 (C)
unnamed: J4.12, Q26.3 (C)
unnamed: J4.9, Q27.3 (C)
unnamed: J4.6, Q28.3 (C)
unnamed: J4.3, Q29.3 (C)
unnamed: J4.2, Q31.3 (C)
unnamed: Q32.2 (B), R112.2
unnamed: Q33.1 (C), R118.2, U7.3 (~latch), U8.3 (~latch), U11.3 (~latch)
unnamed: Q33.2 (B), R117.2
unnamed: R51.1, U5.4 (2)
unnamed: R52.1, U5.7 (3)
unnamed: R53.1, U5.10 (4)
unnamed: R54.1, U5.1 (5)
unnamed: R55.1, U5.2 (1)
unnamed: R56.1, U5.5 (6)
unnamed: R57.1, U5.6 (7)
unnamed: R58.1, U5.9 (8)
unnamed: R59.1, U5.11 (9)
unnamed: R60.1, U6.9 (8)
unnamed: R61.2, U8.11 (OUT6)
unnamed: R62.2, U8.13 (OUT8)
unnamed: R63.2, U8.15 (OUT10)
unnamed: R64.2, U8.17 (OUT12)
unnamed: R65.2, U8.19 (OUT14)
unnamed: R66.2, U8.22 (OUT16)
unnamed: R67.2, U8.24 (OUT18)
unnamed: R68.2, U8.26 (OUT20)
unnamed: R69.2, U8.28 (OUT22)
unnamed: R70.2, U8.30 (OUT24)
unnamed: R71.2, U8.32 (OUT26)
unnamed: R72.2, U8.34 (OUT28)
unnamed: R73.2, U8.36 (OUT30)
unnamed: R74.2, U8.38 (OUT32)
unnamed: R75.2, U3.4
unnamed: R76.2, U2.4
unnamed: R77.2, U7.7 (OUT2)
unnamed: R78.2, U7.9 (OUT4)
unnamed: R79.2, U7.11 (OUT6)
unnamed: R80.2, U7.13 (OUT8)
unnamed: R81.2, U7.15 (OUT10)
unnamed: R82.2, U7.17 (OUT12)
unnamed: R83.2, U7.19 (OUT14)
unnamed: R84.2, U7.22 (OUT16)
unnamed: R85.2, U7.24 (OUT18)
unnamed: R86.2, U7.26 (OUT20)
unnamed: R87.2, U7.28 (OUT22)
unnamed: R88.2, U7.30 (OUT24)
unnamed: R89.2, U7.32 (OUT26)
unnamed: R90.2, U7.34 (OUT28)
unnamed: R91.2, U7.36 (OUT30)
unnamed: R92.2, U7.38 (OUT32)
unnamed: R93.2, U11.7 (OUT2)
unnamed: R94.2, U11.9 (OUT4)
unnamed: R95.2, U11.11 (OUT6)
unnamed: R96.2, U11.13 (OUT8)
unnamed: R97.2, U11.15 (OUT10)
unnamed: R98.2, U11.17 (OUT12)
unnamed: R99.2, U11.19 (OUT14)
unnamed: R100.2, U11.22 (OUT16)
unnamed: R101.1, U5.3 (O)
unnamed: R102.2, U11.24 (OUT18)
unnamed: R103.2, U11.26 (OUT20)
unnamed: R104.2, U11.28 (OUT22)
unnamed: R105.2, U11.30 (OUT24)
unnamed: R106.2, U11.32 (OUT26)
unnamed: R107.2, U11.34 (OUT28)
unnamed: R108.2, U11.36 (OUT30)
unnamed: R109.2, U11.38 (OUT32)
unnamed: R110.2, U8.7 (OUT2)
unnamed: R111.2, U8.9 (OUT4)
unnamed: R112.1, U6.11 (9)
unnamed: R113.1, U9.3 (QD)
unnamed: R113.2, U2.1
unnamed: R114.1, U3.1
unnamed: R114.2, U9.1 (QB)
unnamed: R115.1, U12.1
unnamed: R115.2, U9.15 (QA)
unnamed: R116.1, U13.1
unnamed: R116.2, U9.2 (QC)
unnamed: R117.1, U7.40 (latch), U8.40 (latch), U9.12 (RCLK), U10.11 (HV2), U11.40 (latch)
unnamed: R119.2, U7.6 (OUT1)
unnamed: R120.2, U7.8 (OUT3)
unnamed: R121.2, U7.10 (OUT5)
unnamed: R122.2, U7.12 (OUT7)
unnamed: R123.2, U7.14 (OUT9)
unnamed: R124.2, U7.16 (OUT11)
unnamed: R125.2, U7.18 (OUT13)
unnamed: R126.2, U7.20 (OUT15)
unnamed: R127.2, U7.23 (OUT17)
unnamed: R128.2, U7.25 (OUT19)
unnamed: R129.2, U7.27 (OUT21)
unnamed: R130.2, U7.29 (OUT23)
unnamed: R131.2, U7.31 (OUT25)
unnamed: R132.2, U7.33 (OUT27)
unnamed: R133.2, U7.35 (OUT29)
unnamed: R134.2, U7.37 (OUT31)
unnamed: R135.2, U11.6 (OUT1)
unnamed: R136.2, U11.8 (OUT3)
unnamed: R137.2, U11.10 (OUT5)
unnamed: R138.2, U11.12 (OUT7)
unnamed: R139.2, U11.14 (OUT9)
unnamed: R140.2, U11.16 (OUT11)
unnamed: R141.2, U11.18 (OUT13)
unnamed: R142.2, U11.20 (OUT15)
unnamed: R143.2, U11.23 (OUT17)
unnamed: R144.2, U11.25 (OUT19)
unnamed: R145.2, U11.27 (OUT21)
unnamed: R146.2, U11.29 (OUT23)
unnamed: R147.2, U11.31 (OUT25)
unnamed: R148.2, U11.33 (OUT27)
unnamed: R149.2, U11.35 (OUT29)
unnamed: R150.2, U11.37 (OUT31)
unnamed: R151.2, U8.6 (OUT1)
unnamed: R152.2, U8.8 (OUT3)
unnamed: R153.2, U8.10 (OUT5)
unnamed: R154.2, U8.12 (OUT7)
unnamed: R155.2, U8.14 (OUT9)
unnamed: R156.2, U8.16 (OUT11)
unnamed: R157.2, U8.18 (OUT13)
unnamed: R158.2, U8.20 (OUT15)
unnamed: R159.2, U8.23 (OUT17)
unnamed: R160.2, U8.25 (OUT19)
unnamed: R161.2, U8.27 (OUT21)
unnamed: R162.2, U8.29 (OUT23)
unnamed: R163.2, U8.31 (OUT25)
unnamed: R164.2, U8.33 (OUT27)
unnamed: R165.2, U8.35 (OUT29)
unnamed: R166.2, U8.37 (OUT31)
unnamed: R167.2, U12.4
unnamed: R168.2, U13.4
unnamed: U1.1 (GP0), U10.1 (LV1)
unnamed: U1.2 (GP1), U10.2 (LV2)
unnamed: U1.4 (GP2), U10.5 (LV3)
unnamed: U1.7 (GP5), U6.15 (RESET)
unnamed: U1.9 (GP6), U6.14 (CLOCK)
unnamed: U1.A (USB_SHIELD), U1.B (USB_SHIELD), U1.C (USB_SHIELD), U1.D (USB_SHIELD)
unnamed: U1.6 (GP4), U5.14 (CLOCK)
unnamed: U1.5 (GP3), U5.15 (RESET)
unnamed: U8.41 (SER_OUT), U9.14 (SER)
unnamed: U7.1 (SER_IN), U10.12 (HV1)
unnamed: U7.41 (SER_OUT), U11.1 (SER_IN)
unnamed: U8.1 (SER_IN), U11.41 (SER_OUT)

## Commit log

2022-04-26 fixed dockerfile
2022-04-26 added better text display example, with live feed capability
2022-04-26 formatting changes
2022-04-27 added dockerfile
2022-04-27 added photos
2022-04-27 cropped image
2022-04-27 fixed images
2022-04-27 used better image
2022-04-27 fixed readme
2022-04-27 readme changes
2022-04-27 added proper time output
2022-04-27 added proper rtc
2022-04-28 minor api changes
2022-04-28 added docker-compose file
2022-04-28 updated docs
2022-04-28 modified docker-compose
2022-04-29 added very crude tetris implementation
2022-04-30 bug fixes
2022-05-15 added pcb schematic for HV power supply
2022-05-19 added initial code and pcb project for full graphical conversion
2022-05-24 first draft of full pcb
2022-05-24 mounting holes added and minor pcb changes
2022-06-20 fixed footprint error in pcb and improved ground traces
2022-07-20 updated gerbers
2022-09-02 added rev3 PCB
2022-09-02 added gerbers for rev 3 driver board
2022-09-27 added working PIO-driven control test
2022-10-03 added remote image processing and started with full display anode-wise writing
2022-10-06 first pass image display written, along with on-machine image conversion
2022-10-08 added image hosting API
2022-10-09 changed to PIL for image processing and updated dockerfile
2022-10-11 added image processing to api
2022-10-11 added frame rate control and improved api functionality
2022-10-11 fixed api bugs
2022-10-12 added additional api functionality and refined image parameters
2022-10-17 various improvements to display code
2022-10-19 implemented screen blanking between image fetches
